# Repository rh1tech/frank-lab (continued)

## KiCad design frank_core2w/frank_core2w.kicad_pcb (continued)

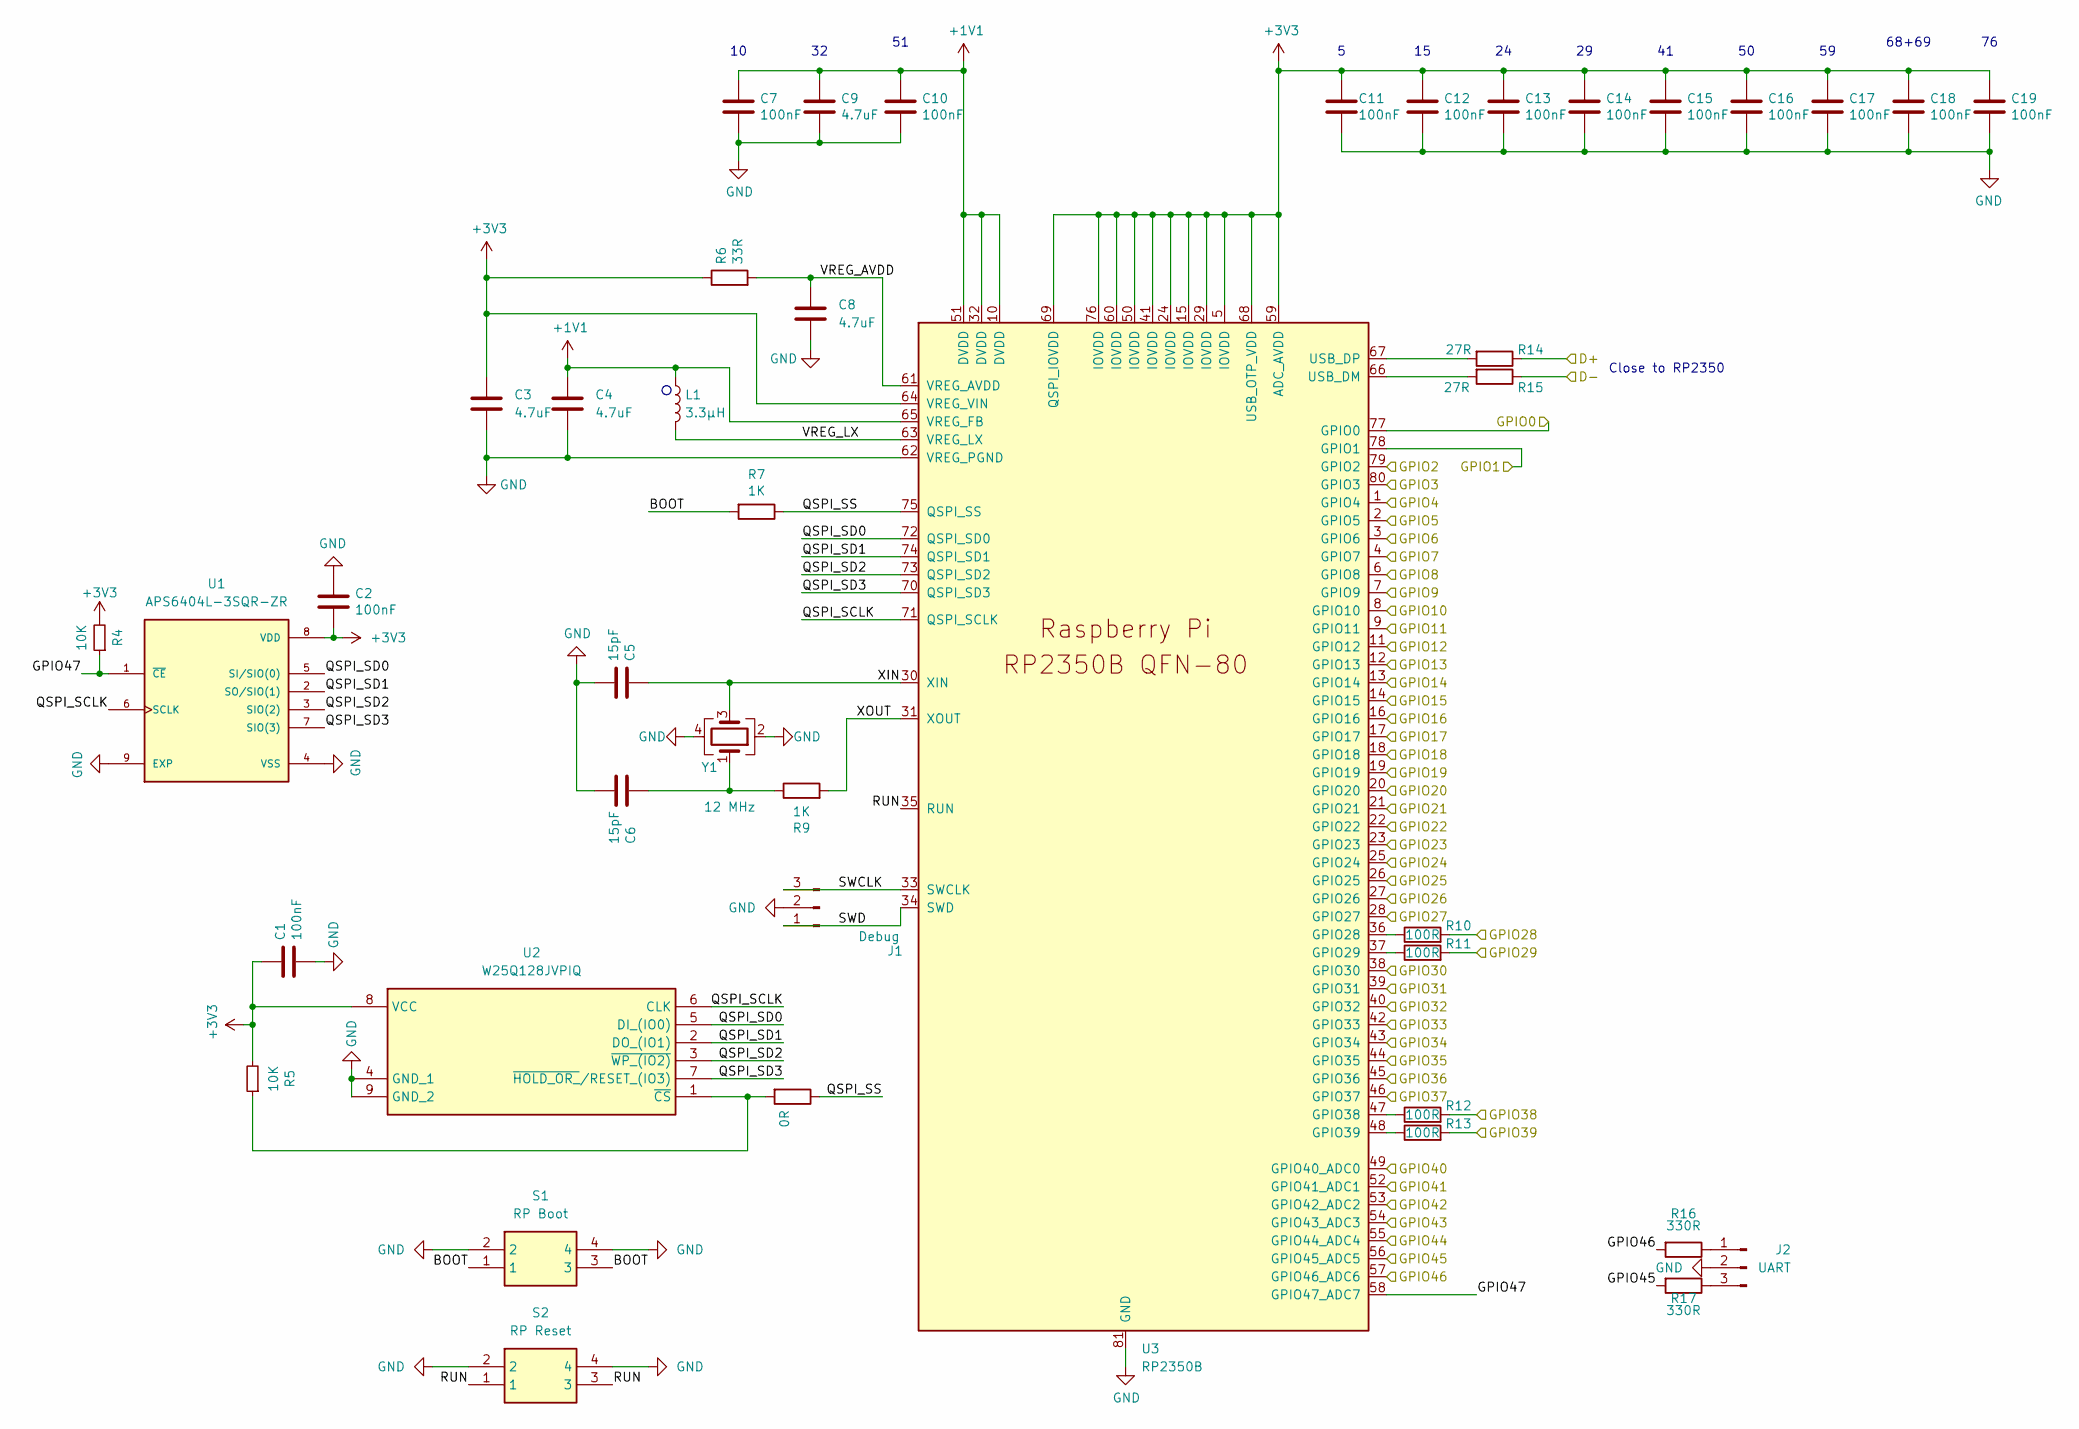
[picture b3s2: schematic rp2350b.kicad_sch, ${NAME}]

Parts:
C1, C2, C7, C10, C11, C12, C13, C14, C15, C16, C17, C18, C19: 100nF; C_0603_1608Metric; LCSC C14663
C3, C4, C8, C9: 4.7uF; C_0603_1608Metric; LCSC C5360844
C5, C6: 15pF; C_0603_1608Metric; LCSC C1644
J1: Debug; JST_SH_1x03_P1.00mm_Vertical; LCSC C160389
J2: UART; JST_SH_1x03_P1.00mm_Vertical; LCSC C160389
L1: 3.3µH; L_AOTA-B201610_2.0x1.6mm; LCSC C98035
R4, R5: 10K; R_0603_1608Metric; LCSC C2906982
R6: 33R; R_0603_1608Metric; LCSC C23140
R7, R9: 1K; R_0603_1608Metric; LCSC C21190
R8: 0R; R_0603_1608Metric; LCSC C21189
R10, R11, R12, R13: 100R; R_0603_1608Metric; LCSC C21190
R14, R15: 27R; R_0603_1608Metric; LCSC C25190
R16, R17: 330R; R_0603_1608Metric
S1: RP Boot; Button_SMD_3x4x2mm; Mouser Part Number 611-KMR221G-LFS; LCSC C36498961
S2: RP Reset; Button_SMD_3x4x2mm; Mouser Part Number 611-KMR221G-LFS; LCSC C36498961
U1: APS6404L-3SQR-ZR; PSON50P200X300X50-9N; PARTREV 2.3; LCSC C3040877
U2: W25Q128JVPIQ; WSON-8-1EP_6x5mm_P1.27mm_EP3.45x4.35mm; Mouser Part Number 454-W25Q128JVPIQ; LCSC C190862
U3: RP2350B; RP2350-QFN-80_10x10_P0.4mm; LCSC C42415655
Y1: 12 MHz; Crystal_SMD_3225-4Pin_3.2x2.5mm; LCSC C9002

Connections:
+1V1: C4.1, C7.1, C9.1, C10.1, L1.1, U3.10 (DVDD), U3.32 (DVDD), U3.51 (DVDD), U3.65 (VREG_FB)
+3V3: C1.1, C2.2, C3.1, C11.1, C12.1, C13.1, C14.1, C15.1, C16.1, C17.1, C18.1, C19.1, R4.2, R5.2, R6.1, U1.8 (VDD), U2.8 (VCC), U3.5 (IOVDD), U3.15 (IOVDD), U3.24 (IOVDD), U3.29 (IOVDD), U3.41 (IOVDD), U3.50 (IOVDD), U3.59 (ADC_AVDD), U3.60 (IOVDD), U3.64 (VREG_VIN), U3.68 (USB_OTP_VDD), U3.69 (QSPI_IOVDD), U3.76 (IOVDD); also elsewhere on the board
/GPIO2/SDA: U3.79 (GPIO2); also elsewhere on the board
/GPIO3/SCL: U3.80 (GPIO3); also elsewhere on the board
/GPIO8/MCLK: U3.6 (GPIO8); also elsewhere on the board
/GPIO9/BCLK: U3.7 (GPIO9); also elsewhere on the board
/GPIO10/WCLK: U3.8 (GPIO10); also elsewhere on the board
/GPIO11/DIN: U3.9 (GPIO11); also elsewhere on the board
/GPIO12/CLKN: U3.11 (GPIO12); also elsewhere on the board
/GPIO13/CLKP: U3.12 (GPIO13); also elsewhere on the board
/GPIO14/D0N: U3.13 (GPIO14); also elsewhere on the board
/GPIO15/D0P: U3.14 (GPIO15); also elsewhere on the board
/GPIO16/D1N: U3.16 (GPIO16); also elsewhere on the board
/GPIO17/D1P: U3.17 (GPIO17); also elsewhere on the board
/GPIO18/D2N: U3.18 (GPIO18); also elsewhere on the board
/GPIO19/D2P: U3.19 (GPIO19); also elsewhere on the board
/RP2350B/BOOT: R7.2, S1.1, S1.3
/RP2350B/D+: R14.1; also elsewhere on the board
/RP2350B/D-: R15.1; also elsewhere on the board
/RP2350B/GPIO38: R12.2; also elsewhere on the board
/RP2350B/GPIO44: U3.55 (GPIO44_ADC4); also elsewhere on the board
/RP2350B/GPIO47: R4.1, U1.1 (~CE), U3.58 (GPIO47_ADC7)
/RP2350B/QSPI_SCLK: U1.6 (SCLK), U2.6 (CLK), U3.71 (QSPI_SCLK)
/RP2350B/QSPI_SD0: U1.5 (SI/SIO(0)), U2.5 (DI_(IO0)), U3.72 (QSPI_SD0)
/RP2350B/QSPI_SD1: U1.2 (SO/SIO(1)), U2.2 (DO_(IO1)), U3.74 (QSPI_SD1)
/RP2350B/QSPI_SD2: U1.3 (SIO(2)), U2.3 (~WP_(IO2)), U3.73 (QSPI_SD2)
/RP2350B/QSPI_SD3: U1.7 (SIO(3)), U2.7 (~HOLD_OR_/RESET_(IO3)), U3.70 (QSPI_SD3)
/RP2350B/QSPI_SS: R7.1, R8.1, U3.75 (QSPI_SS)
/RP2350B/RUN: S2.1, S2.3, U3.35 (RUN)
/RP2350B/SWCLK: J1.3, U3.33 (SWCLK)
/RP2350B/SWD: J1.1, U3.34 (SWD)
/RP2350B/VREG_AVDD: C8.1, R6.2, U3.61 (VREG_AVDD)
/RP2350B/VREG_LX: L1.2, U3.63 (VREG_LX)
/RP2350B/XIN: C5.1, U3.30 (XIN), Y1.3
/RP2350B/XOUT: R9.2, U3.31 (XOUT)
/RP2350/20B/1A/D0: U3.20 (GPIO20); also elsewhere on the board
/RP2350/21B/2A/D1: U3.21 (GPIO21); also elsewhere on the board
/RP2350/22B/3A/D2: U3.22 (GPIO22); also elsewhere on the board
/RP2350/23B/4A/D3: U3.23 (GPIO23); also elsewhere on the board
/RP2350/24B/5A/D4: U3.25 (GPIO24); also elsewhere on the board
/RP2350/25B/6A/D5: U3.26 (GPIO25); also elsewhere on the board
/RP2350/26B/7A/D6: U3.27 (GPIO26); also elsewhere on the board
/RP2350/27B/8A/D7: U3.28 (GPIO27); also elsewhere on the board
/RP2350/28B/9A/CLK: R10.2; also elsewhere on the board
/RP2350/29B/10A/VALID: R11.2; also elsewhere on the board
/RP2350/30B/11A/D0: U3.38 (GPIO30); also elsewhere on the board
/RP2350/31B/12A/D1: U3.39 (GPIO31); also elsewhere on the board
/RP2350/32B/13A/D2: U3.40 (GPIO32); also elsewhere on the board
/RP2350/33B/14A/D3: U3.42 (GPIO33); also elsewhere on the board
/RP2350/34B/15A/D4: U3.43 (GPIO34); also elsewhere on the board
/RP2350/35B/16A/D5: U3.44 (GPIO35); also elsewhere on the board
/RP2350/36B/17A/D6: U3.45 (GPIO36); also elsewhere on the board
/RP2350/37B/18A/D7: U3.46 (GPIO37); also elsewhere on the board
/RP2350/39B/20A/VALID: R13.2; also elsewhere on the board
/RP2350/40B/21A/FS: U3.49 (GPIO40_ADC0); also elsewhere on the board
/RP2350/41B/22A/DB_MS: U3.52 (GPIO41_ADC1); also elsewhere on the board
/RP2350/42B/23A/DB_SM: U3.53 (GPIO42_ADC2); also elsewhere on the board
/RP2350/43B/RUNA/SR: U3.54 (GPIO43_ADC3); also elsewhere on the board
/RP_RX: R17.2, U3.56 (GPIO45_ADC5); also elsewhere on the board
/RP_TX: R16.2, U3.57 (GPIO46_ADC6); also elsewhere on the board
/SD/CD_DAT3/GPIO7: U3.4 (GPIO7); also elsewhere on the board
/SD/CLK/GPIO1: U3.78 (GPIO1); also elsewhere on the board
/SD/CMD/GPIO0: U3.77 (GPIO0); also elsewhere on the board
/SD/DAT0/GPIO4: U3.1 (GPIO4); also elsewhere on the board
/SD/DAT1/GPIO5: U3.2 (GPIO5); also elsewhere on the board
/SD/DAT2/GPIO6: U3.3 (GPIO6); also elsewhere on the board
GND: C1.2, C2.1, C3.2, C4.2, C5.2, C6.2, C7.2, C8.2, C9.2, C10.2, C11.2, C12.2, C13.2, C14.2, C15.2, C16.2, C17.2, C18.2, C19.2, J1.2, J2.2, S1.2, S1.4, S2.2, S2.4, U1.4 (VSS), U1.9 (EXP), U2.4 (GND_1), U2.9 (GND_2), U3.62 (VREG_PGND), U3.81 (GND), Y1.2, Y1.4; also elsewhere on the board
unnamed: C6.1, R9.1, Y1.1
unnamed: J2.1, R16.1
unnamed: J2.3, R17.1
unnamed: R5.1, R8.2, U2.1 (~CS)
unnamed: R10.1, U3.36 (GPIO28)
unnamed: R11.1, U3.37 (GPIO29)
unnamed: R12.1, U3.47 (GPIO38)
unnamed: R13.1, U3.48 (GPIO39)
unnamed: R15.2, U3.66 (USB_DM)
unnamed: R14.2, U3.67 (USB_DP)

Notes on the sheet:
Close to RP2350
68+69

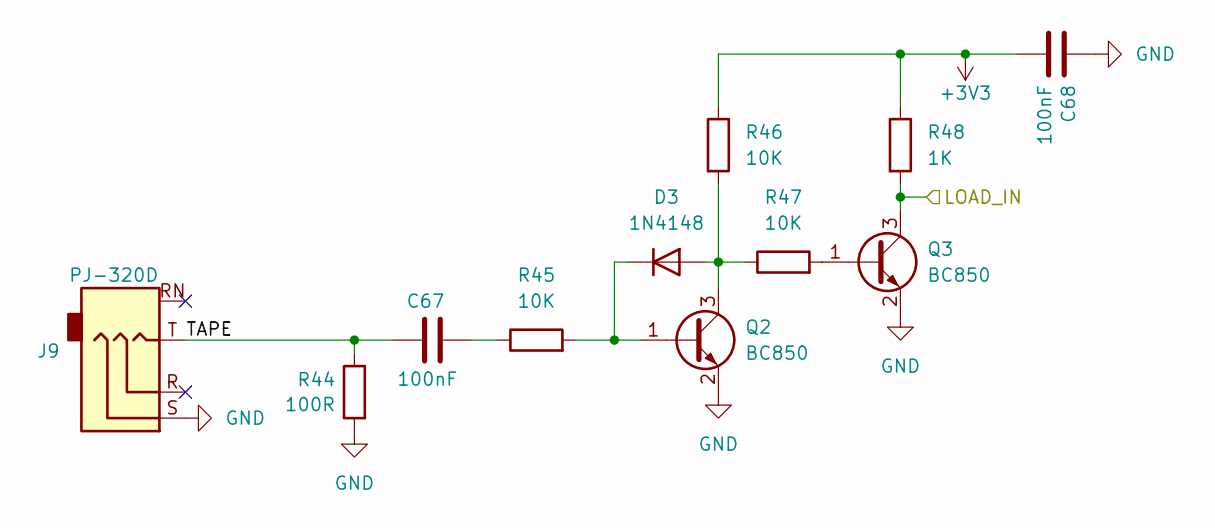
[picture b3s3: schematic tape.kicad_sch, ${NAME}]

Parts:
C67, C68: 100nF; C_0603_1608Metric; LCSC C14663
D3: 1N4148; D_SOD-323; LCSC C2128
J9: PJ-320D; AudioJack_3.5mm_PJ320D_TapeIn; LCSC C431535
Q2, Q3: BC850; SOT-23; LCSC C503377
R44: 100R; R_0603_1608Metric; LCSC C22775
R45, R46, R47: 10K; R_0603_1608Metric; LCSC C2906982
R48: 1K; R_0603_1608Metric; LCSC C21190

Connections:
+3V3: C68.2, R46.1, R48.1; also elsewhere on the board
/RP2350B/GPIO44: Q3.3 (C), R48.2; also elsewhere on the board
/Tape/TAPE: C67.1, J9.T, R44.1
GND: C68.1, J9.S, Q2.2 (E), Q3.2 (E), R44.2; also elsewhere on the board
unnamed: C67.2, R45.1
unnamed: D3.2 (A), Q2.3 (C), R46.2, R47.1
unnamed: D3.1 (K), Q2.1 (B), R45.2
unnamed: Q3.1 (B), R47.2

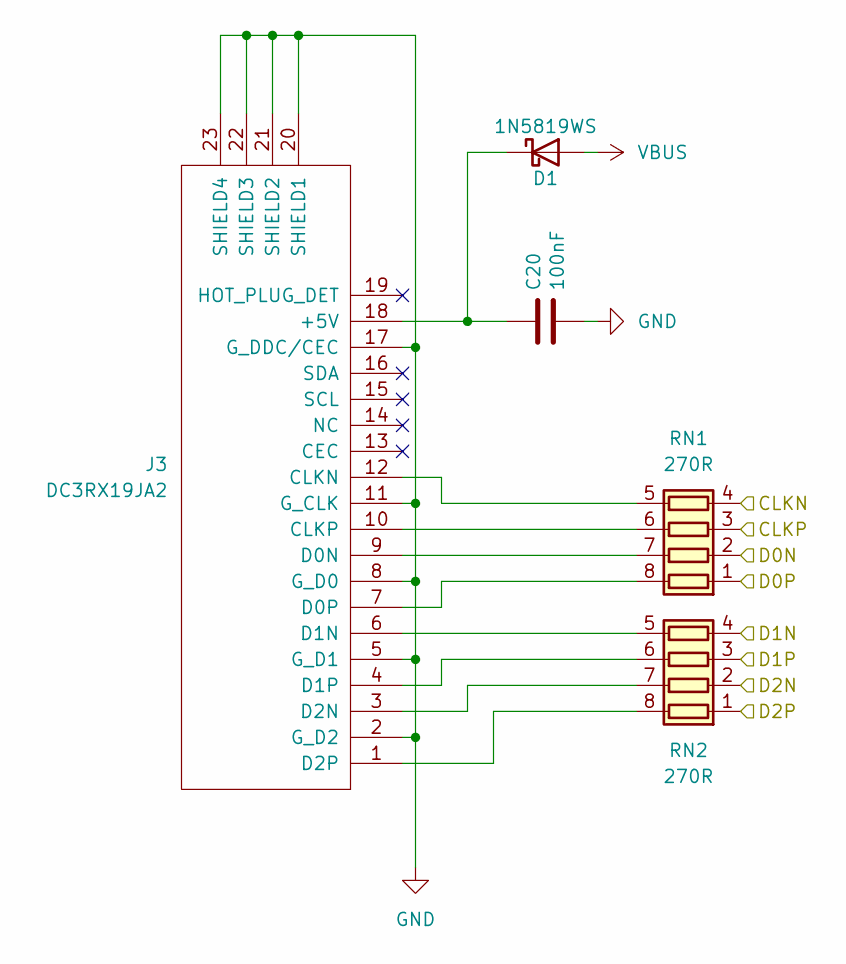
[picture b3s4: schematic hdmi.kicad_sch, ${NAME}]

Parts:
C20: 100nF; C_0603_1608Metric; LCSC C14663
D1: 1N5819WS; D_SOD-323; LCSC C191023
J3: DC3RX19JA2; HDMI_Female
RN1, RN2: 270R; R_Array_4x0603; LCSC C1731063

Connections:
/GPIO12/CLKN: RN1.4 (R4.1); also elsewhere on the board
/GPIO13/CLKP: RN1.3 (R3.1); also elsewhere on the board
/GPIO14/D0N: RN1.2 (R2.1); also elsewhere on the board
/GPIO15/D0P: RN1.1 (R1.1); also elsewhere on the board
/GPIO16/D1N: RN2.4 (R4.1); also elsewhere on the board
/GPIO17/D1P: RN2.3 (R3.1); also elsewhere on the board
/GPIO18/D2N: RN2.2 (R2.1); also elsewhere on the board
/GPIO19/D2P: RN2.1 (R1.1); also elsewhere on the board
GND: C20.2, J3.2 (G_D2), J3.5 (G_D1), J3.8 (G_D0), J3.11 (G_CLK), J3.17 (G_DDC/CEC), J3.20 (SHIELD1), J3.21 (SHIELD2), J3.22 (SHIELD3), J3.23 (SHIELD4); also elsewhere on the board
unnamed: C20.1, D1.1 (K), J3.18 (+5V)
unnamed: J3.12 (CLKN), RN1.5 (R4.2)
unnamed: J3.10 (CLKP), RN1.6 (R3.2)
unnamed: J3.9 (D0N), RN1.7 (R2.2)
unnamed: J3.7 (D0P), RN1.8 (R1.2)
unnamed: J3.6 (D1N), RN2.5 (R4.2)
unnamed: J3.4 (D1P), RN2.6 (R3.2)
unnamed: J3.3 (D2N), RN2.7 (R2.2)
unnamed: J3.1 (D2P), RN2.8 (R1.2)
VBUS: D1.2 (A); also elsewhere on the board

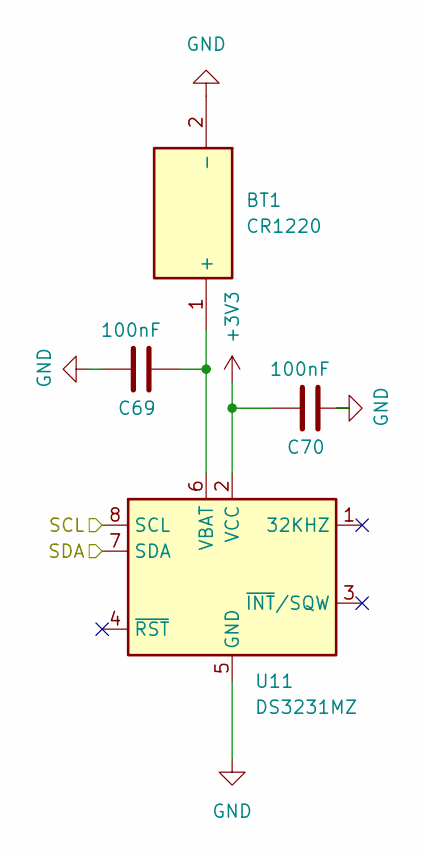
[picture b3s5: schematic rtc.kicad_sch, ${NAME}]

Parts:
BT1: CR1220; Battery_CR1220; Manufacturer_Part_Number 1174; LCSC C5199899
C69, C70: 100nF; C_0603_1608Metric; LCSC C14663
U11: DS3231MZ; SO-8_3.9x4.9mm_P1.27mm; LCSC C107410

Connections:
+3V3: C70.1, U11.2 (VCC); also elsewhere on the board
/GPIO2/SDA: U11.7 (SDA); also elsewhere on the board
/GPIO3/SCL: U11.8 (SCL); also elsewhere on the board
GND: BT1.2 (-), C69.1, C70.2, U11.5 (GND); also elsewhere on the board
unnamed: BT1.1 (+), C69.2, U11.6 (VBAT)

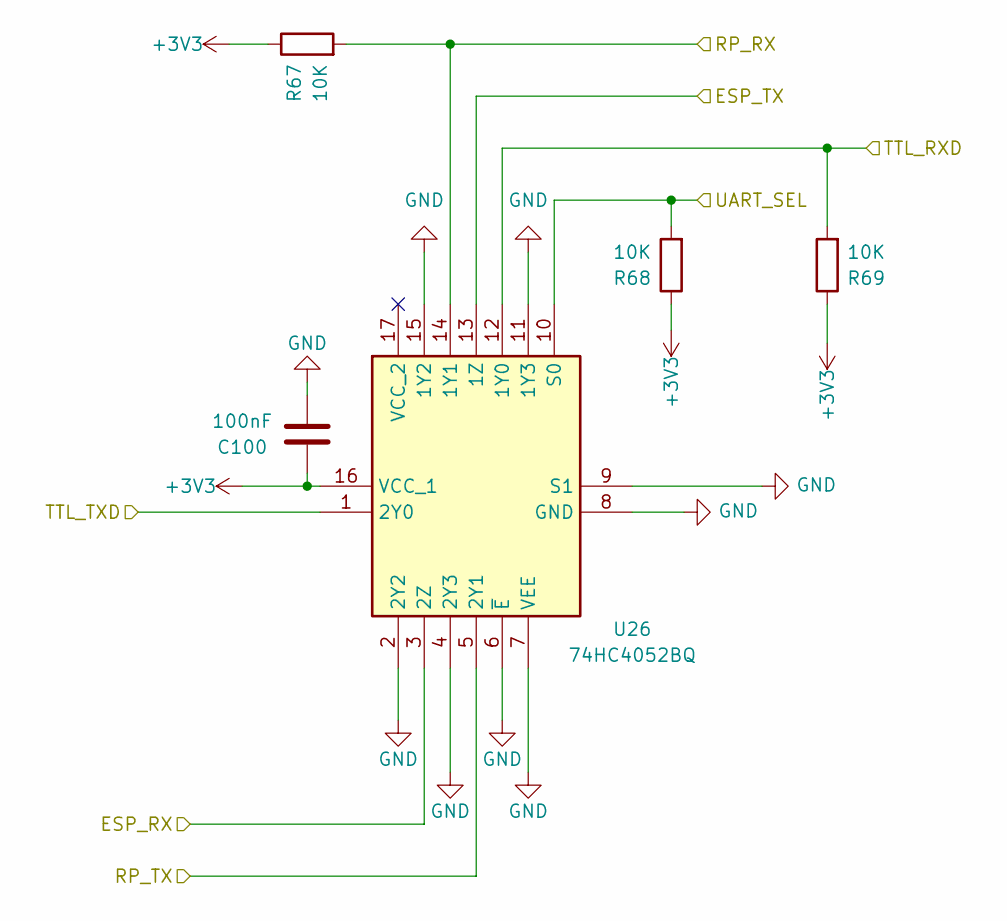
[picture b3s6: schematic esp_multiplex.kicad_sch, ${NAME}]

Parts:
C100: 100nF; C_0603_1608Metric
R67, R68, R69: 10K; R_0603_1608Metric
U26: 74HC4052BQ; 74HC4052BQ115; Mouser Part Number 771-HC4052BQ115

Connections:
+3V3: C100.1, R67.1, R68.1, R69.1, U26.16 (VCC_1); also elsewhere on the board
/ESP8266/RX: U26.3 (2Z); also elsewhere on the board
/ESP8266/TX: U26.13 (1Z); also elsewhere on the board
/RP_RX: R67.2, U26.14 (1Y1); also elsewhere on the board
/RP_TX: U26.5 (2Y1); also elsewhere on the board
/TTL_RXD: R69.2, U26.12 (1Y0); also elsewhere on the board
/TTL_TXD: U26.1 (2Y0); also elsewhere on the board
/UART_SEL: R68.2, U26.10 (S0); also elsewhere on the board
GND: C100.2, U26.2 (2Y2), U26.4 (2Y3), U26.6 (~E), U26.7 (VEE), U26.8 (GND), U26.9 (S1), U26.11 (1Y3), U26.15 (1Y2); also elsewhere on the board

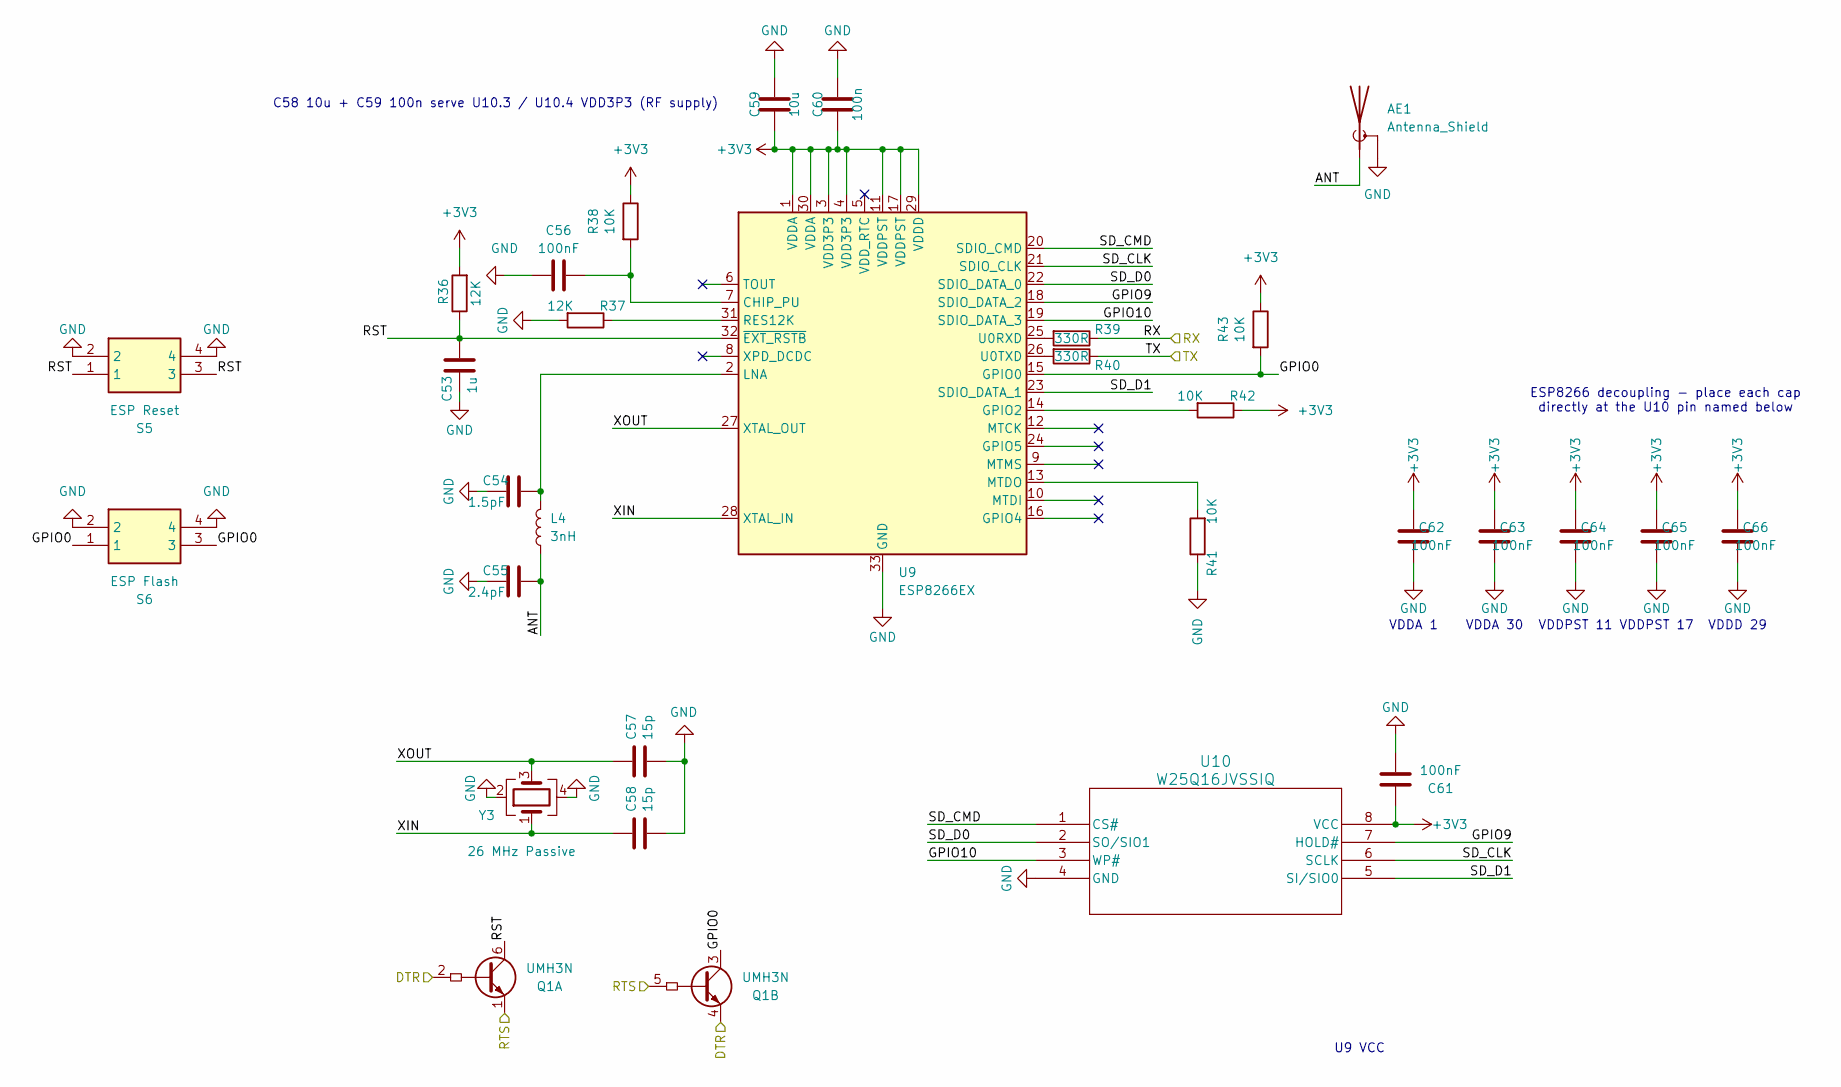
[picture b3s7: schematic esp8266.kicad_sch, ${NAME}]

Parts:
AE1: Antenna_Shield; Antenna_2.4GHz
C53: 1u; C_0603_1608Metric
C54: 1.5pF; C_0603_1608Metric
C55: 2.4pF; C_0603_1608Metric
C56, C61, C62, C63, C64, C65, C66: 100nF; C_0603_1608Metric
C57, C58: 15p; C_0603_1608Metric
C59: 10u; C_0603_1608Metric
C60: 100n; C_0603_1608Metric
L4: 3nH; L_0603_1608Metric
Q1: UMH3N; SOT-363
R36, R37: 12K; R_0603_1608Metric
R38, R41, R42, R43: 10K; R_0603_1608Metric
R39, R40: 330R; R_0603_1608Metric
S5: ESP Reset; Button_SMD_3x4x2mm
S6: ESP Flash; Button_SMD_3x4x2mm; Mouser Part Number 611-KMR221G-LFS
U9: ESP8266EX; QFN-32-1EP_5x5mm_P0.5mm_EP3.45x3.45mm
U10: W25Q16JVSSIQ; SOIC-8
Y3: 26 MHz Passive; Crystal_SMD_3225-4Pin_3.2x2.5mm

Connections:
+3V3: C59.2, C60.2, C61.1, C62.1, C63.1, C64.1, C65.1, C66.1, R36.2, R38.1, R42.1, R43.1, U9.1 (VDDA), U9.3 (VDD3P3), U9.4 (VDD3P3), U9.11 (VDDPST), U9.17 (VDDPST), U9.29 (VDDD), U9.30 (VDDA), U10.8 (VCC); also elsewhere on the board
/ESP8266/ANT: AE1.1 (A), C55.1, L4.1
/ESP8266/GPIO0: Q1.3 (C2), R43.2, S6.1, S6.3, U9.15 (GPIO0)
/ESP8266/GPIO9: U9.18 (SDIO_DATA_2), U10.7 (HOLD#)
/ESP8266/GPIO10: U9.19 (SDIO_DATA_3), U10.3 (WP#)
/ESP8266/RST: C53.1, Q1.6 (C1), R36.1, S5.1, S5.3, U9.32 (~EXT_RSTB)
/ESP8266/RX: R39.1; also elsewhere on the board
/ESP8266/SD_CLK: U9.21 (SDIO_CLK), U10.6 (SCLK)
/ESP8266/SD_CMD: U9.20 (SDIO_CMD), U10.1 (CS#)
/ESP8266/SD_D0: U9.22 (SDIO_DATA_0), U10.2 (SO/SIO1)
/ESP8266/SD_D1: U9.23 (SDIO_DATA_1), U10.5 (SI/SIO0)
/ESP8266/TX: R40.1; also elsewhere on the board
/ESP8266/XIN: C58.1, U9.28 (XTAL_IN), Y3.1
/ESP8266/XOUT: C57.1, U9.27 (XTAL_OUT), Y3.3
/ESP_DTR: Q1.2 (B1), Q1.4 (E2); also elsewhere on the board
/ESP_RTS: Q1.1 (E1), Q1.5 (B2); also elsewhere on the board
GND: AE1.2 (Shield), C53.2, C54.2, C55.2, C56.2, C57.2, C58.2, C59.1, C60.1, C61.2, C62.2, C63.2, C64.2, C65.2, C66.2, R37.2, R41.1, S5.2, S5.4, S6.2, S6.4, U9.33 (GND), U10.4 (GND), Y3.2, Y3.4; also elsewhere on the board
unnamed: C56.1, R38.2, U9.7 (CHIP_PU)
unnamed: R42.2, U9.14 (GPIO2)
unnamed: C54.1, L4.2, U9.2 (LNA)
unnamed: R41.2, U9.13 (MTDO)
unnamed: R37.1, U9.31 (RES12K)
unnamed: R39.2, U9.25 (U0RXD)
unnamed: R40.2, U9.26 (U0TXD)

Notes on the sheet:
VDDD 29
U9 VCC
VDDA 30
C58 10u + C59 100n serve U10.3 / U10.4 VDD3P3 (RF supply)
ESP8266 decoupling - place each cap directly at the U10 pin named below
VDDPST 17
VDDPST 11
VDDA 1

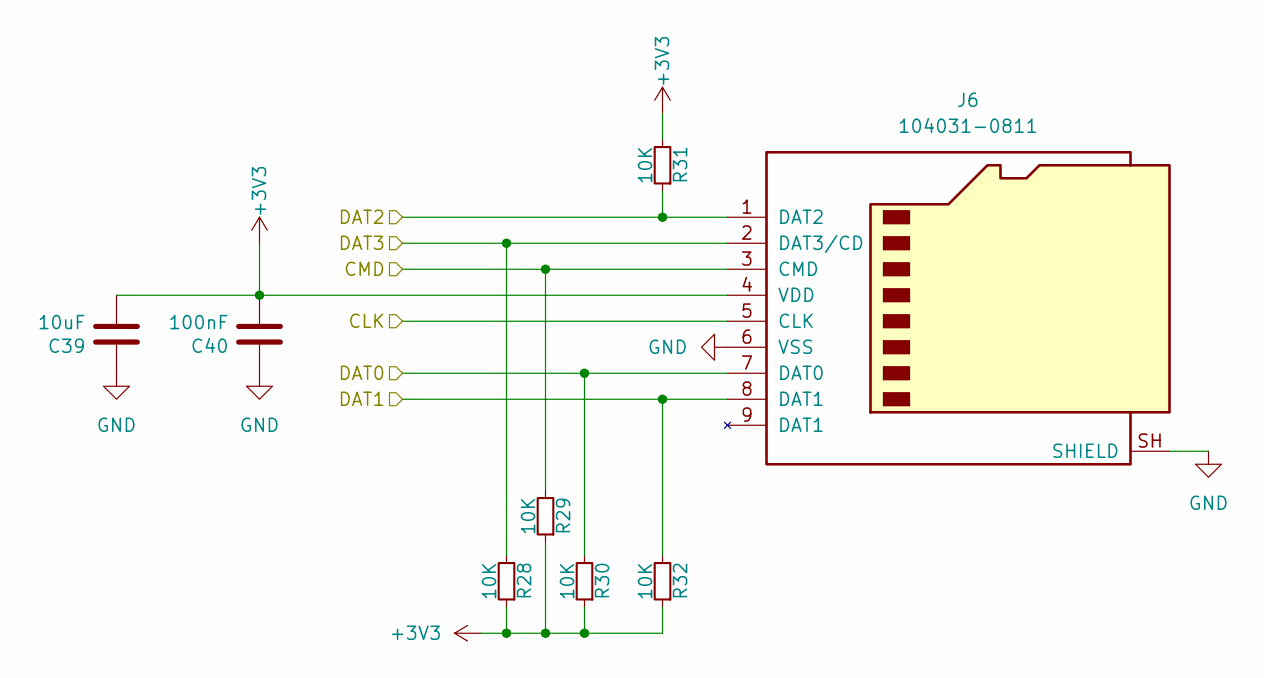
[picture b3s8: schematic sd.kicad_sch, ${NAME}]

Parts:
C39: 10uF; C_0603_1608Metric; LCSC C96446
C40: 100nF; C_0603_1608Metric; LCSC C14663
J6: 104031-0811; MicroSD_SMD_Long; LCSC C585350
R28, R29, R30, R31, R32: 10K; R_0603_1608Metric; LCSC C2906982

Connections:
+3V3: C39.2, C40.2, J6.4 (VDD), R28.1, R29.1, R30.1, R31.2, R32.1; also elsewhere on the board
/SD/CD_DAT3/GPIO7: J6.2 (DAT3/CD), R28.2; also elsewhere on the board
/SD/CLK/GPIO1: J6.5 (CLK); also elsewhere on the board
/SD/CMD/GPIO0: J6.3 (CMD), R29.2; also elsewhere on the board
/SD/DAT0/GPIO4: J6.7 (DAT0), R30.2; also elsewhere on the board
/SD/DAT1/GPIO5: J6.8 (DAT1), R32.2; also elsewhere on the board
/SD/DAT2/GPIO6: J6.1 (DAT2), R31.1; also elsewhere on the board
GND: C39.1, C40.1, J6.6 (VSS), J6.SH (SHIELD); also elsewhere on the board

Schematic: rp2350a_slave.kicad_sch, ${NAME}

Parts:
C21, C26, C29, C30, C31, C32, C33, C34, C35, C36, C37, C38: 100nF; C_0603_1608Metric; LCSC C14663
C22, C25, C27, C28: 4.7uF; C_0603_1608Metric; LCSC C5360844
C23, C24: 15pF; C_0603_1608Metric; LCSC C1644
D2: 1N5819WS; D_SOD-323; LCSC C191023
J4: Debug; JST_SH_1x03_P1.00mm_Vertical; LCSC C160389
J5: UART; JST_SH_1x03_P1.00mm_Vertical; LCSC C160389
L2: 3.3µH; L_AOTA-B201610_2.0x1.6mm; LCSC C98035
LD1: Blue; LED_0603_1608Metric
LD2: WS2812B-2020; LED_WS2812B-2020_PLCC4_2.0x2.0mm; LCSC C965555
R18, R23: 10K; R_0603_1608Metric; LCSC C2906982
R19, R21, R26: 1K; R_0603_1608Metric; LCSC C21190
R20: 33R; R_0603_1608Metric; LCSC C23140
R22: 0R; R_0603_1608Metric; LCSC C21189
R24, R25: 27R; R_0603_1608Metric; LCSC C25190
R27: 330R; R_0603_1608Metric; LCSC C23138
S3: RP Boot; Button_SMD_3x4x2mm; Mouser Part Number 611-KMR221G-LFS; LCSC C36498961
S4: RP Reset; Button_SMD_3x4x2mm; Mouser Part Number 611-KMR221G-LFS; LCSC C36498961
U4: W25Q128JVPIQ; WSON-8-1EP_6x5mm_P1.27mm_EP3.45x4.35mm; Mouser Part Number 454-W25Q128JVPIQ; LCSC C190862
U5: RP2350; QFN-60-1EP_7x7mm_P0.4mm_EP3.4x3.4mm
U6: APS6404L-3SQR-ZR; PSON50P200X300X50-9N; PARTREV 2.3; LCSC C3040877
Y2: 12 MHz; Crystal_SMD_3225-4Pin_3.2x2.5mm; LCSC C9002

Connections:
+1V1_A: C25.1, C26.1, C28.1, C29.1, L2.1, U5.6 (DVDD), U5.23 (DVDD), U5.39 (DVDD), U5.50 (VREG_FB)
+3V3: C21.1, C22.1, C30.2, C31.1, C32.1, C33.1, C34.1, C35.1, C36.1, C37.1, R18.2, R20.1, R23.2, U4.8 (VCC), U5.1 (IOVDD), U5.11 (IOVDD), U5.20 (IOVDD), U5.30 (IOVDD), U5.38 (IOVDD), U5.44 (ADC_AVDD), U5.45 (IOVDD), U5.49 (VREG_VIN), U5.53 (USB_OTP_VDD), U5.54 (QSPI_IOVDD), U6.8 (VDD); also elsewhere on the board
/RP2350A/BOOT: R21.2, S3.1, S3.3
/RP2350A/D+: R24.1; also elsewhere on the board
/RP2350A/D-: R25.1; also elsewhere on the board
/RP2350A/GPIO0: R23.1, U5.2 (GPIO0), U6.1 (~CE)
/RP2350A/GPIO9: U5.13 (GPIO9); also elsewhere on the board
/RP2350A/GPIO24/UART_1: J5.1, U5.36 (GPIO24)
/RP2350A/GPIO25/UART_3: J5.3, U5.37 (GPIO25)
/RP2350A/GPIO28: U5.42 (GPIO28_ADC2)
/RP2350A/GPIO29: U5.43 (GPIO29_ADC3)
/RP2350A/QSPI_SCLK: U4.6 (CLK), U5.56 (QSPI_SCLK), U6.6 (SCLK)
/RP2350A/QSPI_SD0: U4.5 (DI_(IO0)), U5.57 (QSPI_SD0), U6.5 (SI/SIO(0))
/RP2350A/QSPI_SD1: U4.2 (DO_(IO1)), U5.59 (QSPI_SD1), U6.2 (SO/SIO(1))
/RP2350A/QSPI_SD2: U4.3 (~WP_(IO2)), U5.58 (QSPI_SD2), U6.3 (SIO(2))
/RP2350A/QSPI_SD3: U4.7 (~HOLD_OR_/RESET_(IO3)), U5.55 (QSPI_SD3), U6.7 (SIO(3))
/RP2350A/QSPI_SS: R21.1, R22.1, U5.60 (QSPI_SS)
/RP2350A/SWCLK: J4.3, U5.24 (SWCLK)
/RP2350A/SWD: J4.1, U5.25 (SWD)
/RP2350A/VREG_AVDD: C27.1, R20.2, U5.46 (VREG_AVDD)
/RP2350A/VREG_LX: L2.2, U5.48 (VREG_LX)
/RP2350A/XIN: C23.1, U5.21 (XIN), Y2.3
/RP2350A/XOUT: R19.2, U5.22 (XOUT)
/RP2350/20B/1A/D0: U5.3 (GPIO1); also elsewhere on the board
/RP2350/21B/2A/D1: U5.4 (GPIO2); also elsewhere on the board
/RP2350/22B/3A/D2: U5.5 (GPIO3); also elsewhere on the board
/RP2350/23B/4A/D3: U5.7 (GPIO4); also elsewhere on the board
/RP2350/24B/5A/D4: U5.8 (GPIO5); also elsewhere on the board
/RP2350/25B/6A/D5: U5.9 (GPIO6); also elsewhere on the board
/RP2350/26B/7A/D6: U5.10 (GPIO7); also elsewhere on the board
/RP2350/27B/8A/D7: U5.12 (GPIO8); also elsewhere on the board
/RP2350/29B/10A/VALID: U5.14 (GPIO10); also elsewhere on the board
/RP2350/30B/11A/D0: U5.15 (GPIO11); also elsewhere on the board
/RP2350/31B/12A/D1: U5.16 (GPIO12); also elsewhere on the board
/RP2350/32B/13A/D2: U5.17 (GPIO13); also elsewhere on the board
/RP2350/33B/14A/D3: U5.18 (GPIO14); also elsewhere on the board
/RP2350/34B/15A/D4: U5.19 (GPIO15); also elsewhere on the board
/RP2350/35B/16A/D5: U5.27 (GPIO16); also elsewhere on the board
/RP2350/36B/17A/D6: U5.28 (GPIO17); also elsewhere on the board
/RP2350/37B/18A/D7: U5.29 (GPIO18); also elsewhere on the board
/RP2350/38B/19A/CLK: U5.31 (GPIO19); also elsewhere on the board
/RP2350/39B/20A/VALID: U5.32 (GPIO20); also elsewhere on the board
/RP2350/40B/21A/FS: U5.33 (GPIO21); also elsewhere on the board
/RP2350/41B/22A/DB_MS: U5.34 (GPIO22); also elsewhere on the board
/RP2350/42B/23A/DB_SM: U5.35 (GPIO23); also elsewhere on the board
/RP2350/43B/RUNA/SR: S4.1, S4.3, U5.26 (RUN); also elsewhere on the board
GND: C21.2, C22.2, C23.2, C24.2, C25.2, C26.2, C27.2, C28.2, C29.2, C30.1, C31.2, C32.2, C33.2, C34.2, C35.2, C36.2, C37.2, C38.2, J4.2, J5.2, LD1.1 (K), LD2.2 (VSS), S3.2, S3.4, S4.2, S4.4, U4.4 (GND_1), U4.9 (GND_2), U5.47 (VREG_PGND), U5.61 (GND), U6.4 (VSS), U6.9 (EXP), Y2.2, Y2.4; also elsewhere on the board
unnamed: C24.1, R19.1, Y2.1
unnamed: C38.1, D2.1 (K), LD2.4 (VDD)
unnamed: LD1.2 (A), R26.1
unnamed: LD2.3 (DIN), R27.1
unnamed: R18.1, R22.2, U4.1 (~CS)
unnamed: R26.2, U5.40 (GPIO26_ADC0)
unnamed: R27.2, U5.41 (GPIO27_ADC1)
unnamed: R25.2, U5.51 (USB_DM)
unnamed: R24.2, U5.52 (USB_DP)
VBUS: D2.2 (A); also elsewhere on the board

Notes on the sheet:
44+45
Make sure these are close to RP2350
53+54

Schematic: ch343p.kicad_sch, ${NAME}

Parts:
C92, C93, C94: 100nF; C_0603_1608Metric; LCSC C14663
LD4: Orange; LED_0603_1608Metric; LCSC C965800
R64: 1K; R_0603_1608Metric; LCSC C21190
U20: CH343P; WCH_QFN-16-1EP_3x3mm_P0.5mm_EP1.8x1.8mm; LCSC C2846043

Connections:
+3V3: C94.2, R64.2, U20.1 (VIO); also elsewhere on the board
/CH343P/UD+: U20.7 (UD+); also elsewhere on the board
/CH343P/UD-: U20.8 (UD-); also elsewhere on the board
/ESP_DTR: U20.12 (~DTR); also elsewhere on the board
/ESP_RTS: U20.13 (~RTS); also elsewhere on the board
/TTL_RXD: U20.5 (RXD); also elsewhere on the board
/TTL_TXD: U20.4 (TXD); also elsewhere on the board
GND: C92.1, C93.1, C94.1, U20.2 (GND), U20.17 (GND_EPAD); also elsewhere on the board
unnamed: LD4.2 (A), R64.1
unnamed: LD4.1 (K), U20.10 (~ACT)
unnamed: C93.2, U20.6 (V3_{OUT})
VBUS: C92.2, U20.3 (VDD5), U20.9 (VBUS); also elsewhere on the board

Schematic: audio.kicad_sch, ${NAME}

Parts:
C41, C42, C46, C49, C50: 100nF; C_0603_1608Metric; LCSC C14663
C43, C44: 100uF; C_1206_3216Metric; LCSC C7432784
C45, C47, C48: 10uF; C_0603_1608Metric; LCSC C96446
C51, C52: 1uF; C_0603_1608Metric; LCSC C29936
J7: PJ-320D; AudioJack_3.5mm_PJ320D_AudioOut; LCSC C431535
J8: Speaker; JST_GH_1x02_P1.25mm
L3: 330R 2A; L_0805_2012Metric; LCSC C76819
R33, R34: 4.7K; R_0603_1608Metric; LCSC C23162
R35: 10K; R_0603_1608Metric; LCSC C2906982
U7: TLV320DAC3100IRHBR; Mouser Part Number 595-V320DAC3100IRHBR; LCSC C179677
U8: XC6206P182MR-G; Mouser Part Number 865-XC6206P182MR-G; LCSC C347373

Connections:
+1V8: C42.2, C51.2, U7.3 (DVDD), U8.2 (VOUT)
+3V3: C41.1, C45.2, C46.2, C47.2, C49.2, C52.2, R33.2, R34.2, R35.2, U7.2 (IOVDD), U7.17 (AVDD), U7.28 (HPVDD), U8.3 (VIN); also elsewhere on the board
/Audio/+5V_SPK: C48.2, C50.2, L3.1, U7.21 (SPKVDD_1), U7.24 (SPKVDD_2)
/Audio/SPKM: J8.2, U7.19 (SPKM_1), U7.23 (SPKM_2)
/Audio/SPKP: J8.1, U7.22 (SPKP_1), U7.26 (SPKP_2)
/GPIO2/SDA: R34.1, U7.9 (SDA); also elsewhere on the board
/GPIO3/SCL: R33.1, U7.10 (SCL); also elsewhere on the board
/GPIO8/MCLK: U7.8 (MCLK); also elsewhere on the board
/GPIO9/BCLK: U7.7 (BCLK); also elsewhere on the board
/GPIO10/WCLK: U7.6 (WCLK); also elsewhere on the board
/GPIO11/DIN: U7.5 (DIN); also elsewhere on the board
GND: C41.2, C42.1, C45.1, C46.1, C47.1, C48.1, C49.1, C50.1, C51.1, C52.1, J7.S, U7.1 (IOVSS), U7.16 (AVSS), U7.18 (DVSS), U7.20 (SPKVSS_1), U7.25 (SPKVSS_2), U7.29 (HPVSS), U7.33 (EP), U8.1 (VSS); also elsewhere on the board
unnamed: C43.1, J7.R
unnamed: C44.1, J7.T
unnamed: C44.2, U7.27 (HPL)
unnamed: C43.2, U7.30 (HPR)
unnamed: R35.1, U7.31 (~RESET)
VBUS: L3.2; also elsewhere on the board
